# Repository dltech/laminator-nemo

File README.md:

# laminator-nemo
simple replacement board for office laminator with display, temperature and motor control.

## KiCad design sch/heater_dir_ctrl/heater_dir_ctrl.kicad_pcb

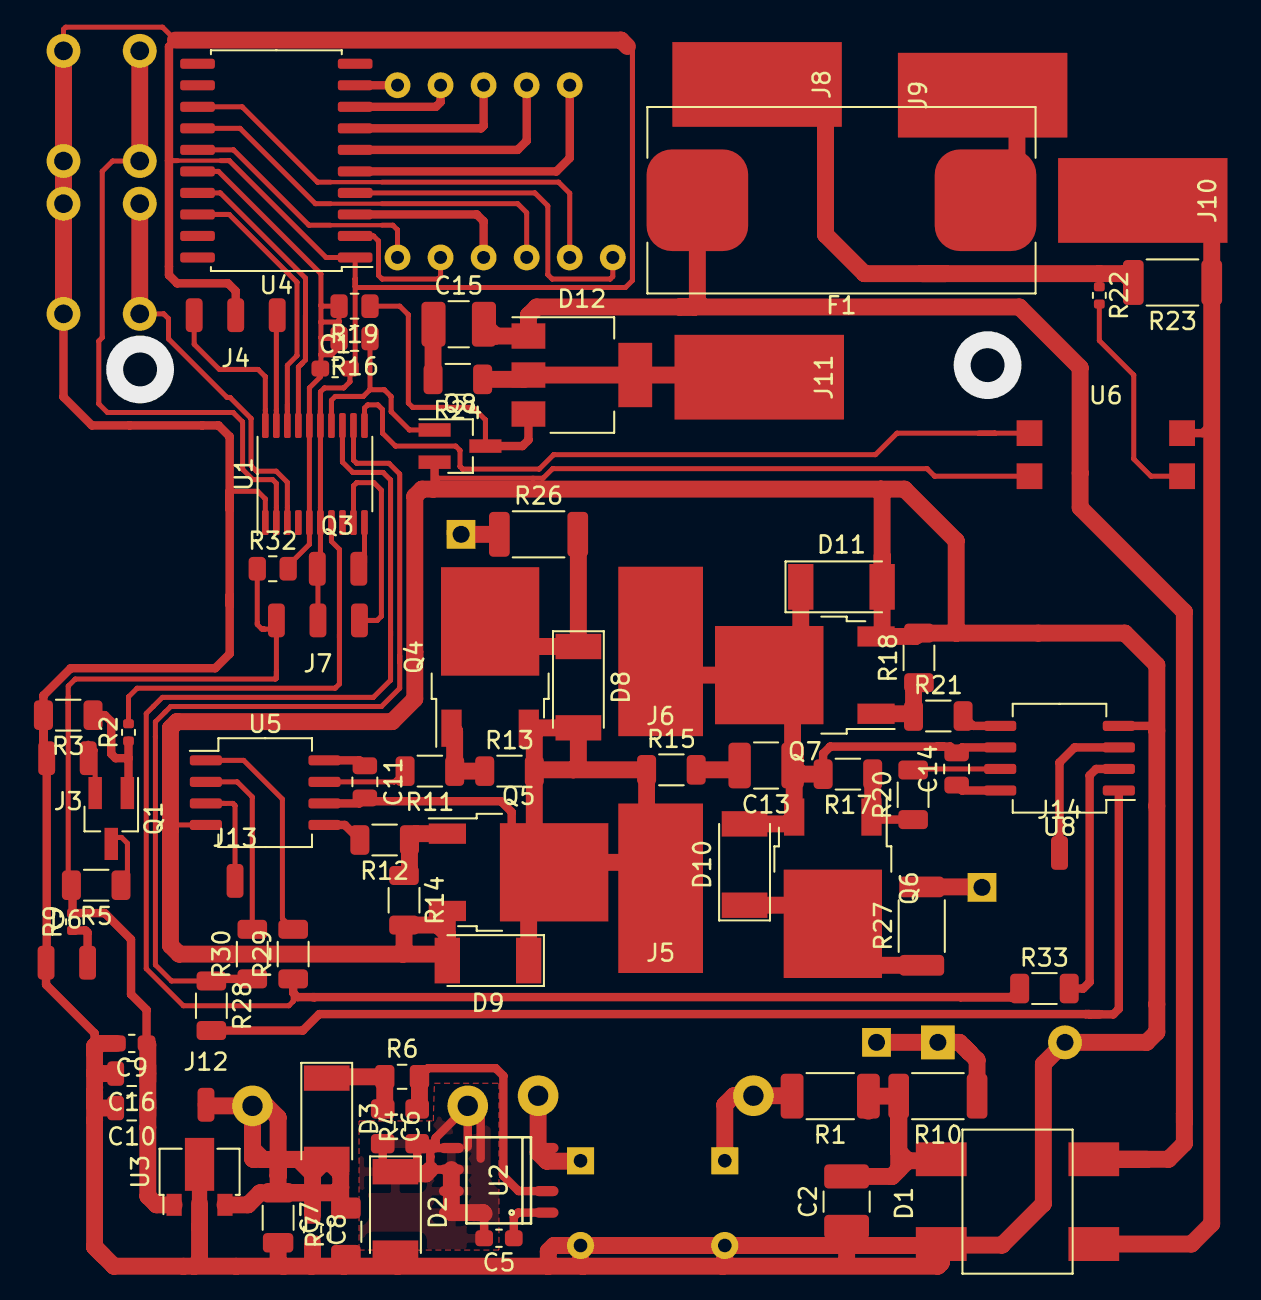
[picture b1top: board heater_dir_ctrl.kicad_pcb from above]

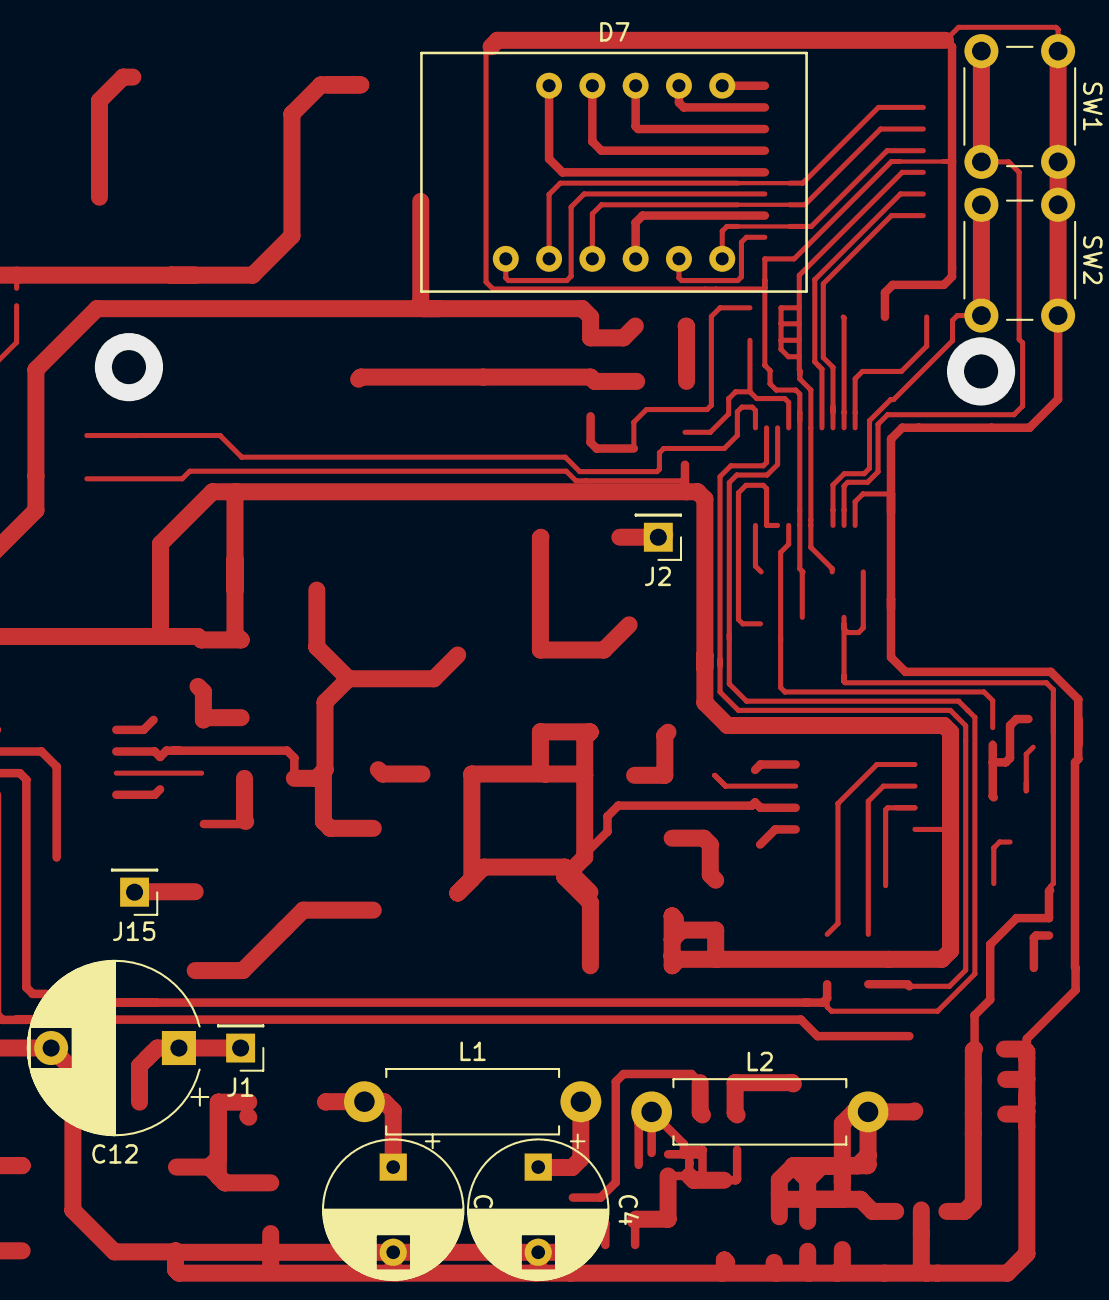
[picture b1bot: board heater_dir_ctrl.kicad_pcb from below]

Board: 2 copper layers, 90 parts (11 on the bottom side), 69 nets.

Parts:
C1, C5, C8, C9: 100n; C_0603_1608Metric_Pad1.05x0.95mm_HandSolder
C2: 0.1; C_1210_3225Metric_Pad1.42x2.65mm_HandSolder
C3, C4: 4.7uF 400V; CP_Radial_D8.0mm_P5.00mm
C6: 1uF; C_0805_2012Metric_Pad1.15x1.40mm_HandSolder
C7: 100uF; C_1206_3216Metric
C10, C11, C14, C16: 10uF; C_0805_2012Metric
C12: 22uF 400V; CP_Radial_D10.0mm_P7.50mm
C13: 100n; C_1210_3225Metric_Pad1.33x2.70mm_HandSolder
C15: 100n; C_1210_3225Metric_Pad1.42x2.65mm_HandSolder
D1: D_Bridge_+-AA; DB-1S
D2: S1M; D_MELF
D3, D8, D9, D10, D11: 1N4007; D_MELF
D6: IR204A; 2WIRE_PADS
D7: LED_3digit; FYT-3631_nonc
D12: Z0109MN; SOT-223
F1: Fuse; Fuseholder_Cylinder-5x20mm_Schurter_OGN-SMD_Horizontal_Open
J1, J2, J15: 300V; PinHeader_1x01_P2.54mm_Vertical
J3: UV; 2WIRE_PADS
J4: SWD; 3WIRE_PADS
J5, J6: motor; SolderWirePad_1x01_SMD_5x10mm
J7: .; 3WIRE_PADS
J8, J9: ac_in; SolderWirePad_1x01_SMD_5x10mm
J10, J11: heater; SolderWirePad_1x01_SMD_5x10mm
J12, J13, J14: 10V; SolderWirePad_1x01_SMD_1x2mm
L1, L2: L; R_Axial_DIN0411_L9.9mm_D3.6mm_P12.70mm_Horizontal
Q1: AO3400; SOT-23_Handsoldering
Q3: Q_Photo_NPN_CE; 2WIRE_PADS
Q4, Q5, Q6, Q7: 2N60; TO-252-2
Q8: DTD114E; SOT-23_Handsoldering
R1: 10; R_2010_5025Metric
R2: 50; R_0402_1005Metric
R3: 50; R_1206_3216Metric
R4: 2.2k; R_0805_2012Metric_Pad1.15x1.40mm_HandSolder
R5, R11, R12, R13, R14, R15, R17, R18, R20, R21, R28, R29, R30, R33: 220; R_1206_3216Metric
R6: 4.7k; R_0805_2012Metric_Pad1.15x1.40mm_HandSolder
R7: 2.2k; R_1206_3216Metric
R9: 1k; R_0402_1005Metric
R10: 100; R_2010_5025Metric
R16, R19: 100k; R_0805_2012Metric
R22: 1к; R_0402_1005Metric
R23, R26, R27: 1; R_2010_5025Metric
R24: 1k; R_1206_3216Metric
R32: 2; R_0805_2012Metric
SW1, SW2: SW_Push; SW_PUSH_6mm
U1: STM32F031F4P6; TSSOP-20_4.4x6.5mm_P0.65mm
U2: LNK306D; SO-8C
U3: L78L33_SOT89; SOT-89-3
U4: TM1637; SOIC-20W_7.5x12.8mm_P1.27mm
U5, U8: L6388; SO-8_5.3x6.2mm_P1.27mm
U6: LTV-817; LTV817

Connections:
+3.3VA: C9.1, C10.1, C16.1, J7.3, R5.2, R9.2, R32.1, U3.1
+3V3: C1.1, R16.2, R19.2, R32.2, U1.5, U1.16, U4.16
+10V: C7.1, C8.1, D3.2, J12.1, J13.1, J14.1, L2.2, R7.2, U3.3, U5.3, U8.3
/LEFT: R28.1, R30.1, U1.12
/RIGHT: R29.1, R33.1, U1.13
DS18B20: J7.1, U1.8, U1.9
GND: C1.2, C2.1, C3.2, C4.2, C7.2, C8.2, C9.2, C10.2, C12.2, C16.2, D1.2, D2.2, D6.1, D9.2, D11.2, J3.2, J4.2, J7.2, Q3.1, Q5.3, Q7.3, Q8.2, R3.2, R7.1, R14.2, R18.2, SW1.1, SW2.1, U1.1, U1.6, U1.15, U3.2, U4.1, U5.4, U6.3, U8.4
LINE: D1.3, J10.1, R23.1, U6.2
NEUT: C15.2, D1.4, D12.1, F1.2
unnamed: C3.1, L1.1, R1.2
unnamed: C4.1, L1.2, U2.4
unnamed: C5.1, U2.1
unnamed: C5.2, C6.2, D2.1, L2.1, R4.1, U2.5, U2.6, U2.7, U2.8
unnamed: C6.1, D3.1, R6.1
unnamed: C11.1, U5.8
unnamed: C11.2, D8.2, D9.1, J5.1, Q4.3, Q5.2, R13.2, R15.1, U5.6
unnamed: C12.1, J1.1, R10.1
unnamed: C13.1, C14.2, D10.2, D11.1, J6.1, Q6.3, Q7.2, R17.2, U8.6
unnamed: C13.2, R15.2
unnamed: C14.1, U8.8
unnamed: C15.1, R24.2
unnamed: D6.2, R9.1
unnamed: D7.1, U4.9
unnamed: D7.2, U4.8
unnamed: D7.3, U4.7
unnamed: D7.4, U4.6
unnamed: D7.5, U4.5
unnamed: D7.7, U4.4
unnamed: D7.8, U4.13
unnamed: D7.9, U4.14
unnamed: D7.10, U4.3
unnamed: D7.11, U4.2
unnamed: D7.12, U4.15
unnamed: D8.1, Q4.2, R26.2
unnamed: D10.1, Q6.2, R27.1
unnamed: D12.2, D12.4, J11.1, R24.1
unnamed: D12.3, Q8.3, R19.1
unnamed: F1.1, J9.1
unnamed: J2.1, R26.1
unnamed: J3.1, Q1.2
unnamed: J4.1, U1.19
unnamed: J4.3, U1.20
unnamed: J8.1, R22.1, R23.2
unnamed: J15.1, R27.2
unnamed: Q1.1, R2.1, R3.1
unnamed: Q1.3, R5.1
unnamed: Q3.2, U1.10
unnamed: Q4.1, R11.1, R13.1
unnamed: Q5.1, R12.1, R14.1
unnamed: Q6.1, R17.1, R20.1
unnamed: Q7.1, R18.1, R21.1
unnamed: Q8.1, R16.1, U1.14
unnamed: R2.2, U1.7
unnamed: R4.2, R6.2, U2.2
unnamed: R11.2, U5.7
unnamed: R12.2, U5.5
unnamed: R20.2, U8.7
unnamed: R21.2, U8.5
unnamed: R22.2, U6.1
unnamed: R28.2, U8.1
unnamed: R29.2, U5.1
unnamed: R30.2, U5.2
unnamed: R33.2, U8.2
unnamed: SW1.2, U1.2
unnamed: SW2.2, U1.3
unnamed: U1.11, U6.4
unnamed: U1.17, U4.17
unnamed: U1.18, U4.18
VPP: C2.2, D1.1, R1.1, R10.2

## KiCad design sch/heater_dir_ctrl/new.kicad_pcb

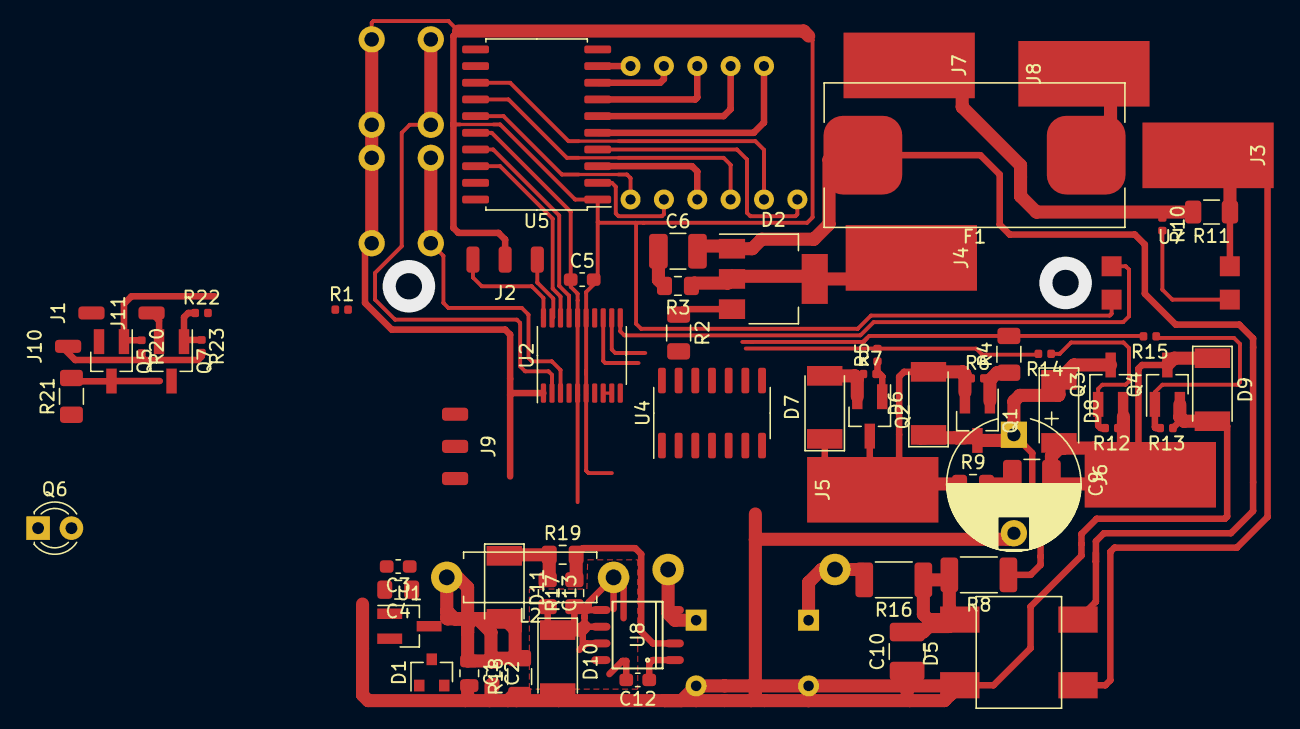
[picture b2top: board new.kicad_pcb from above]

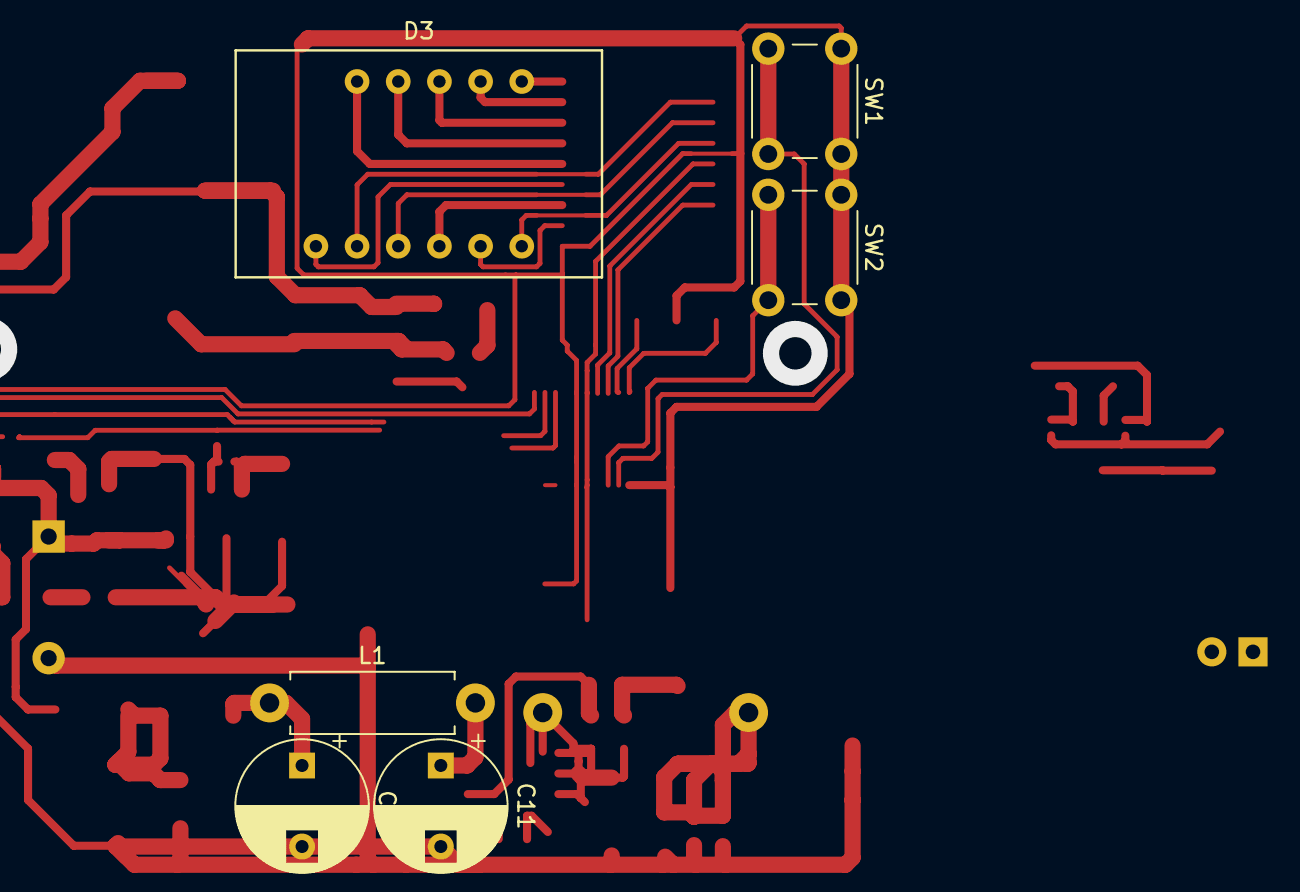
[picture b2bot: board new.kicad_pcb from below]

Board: 2 copper layers, 75 parts (6 on the bottom side), 60 nets.

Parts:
C1: 10uF; C_0805_2012Metric
C2, C3, C5, C12: 100n; C_0603_1608Metric_Pad1.05x0.95mm_HandSolder
C4: 10uF; C_0805_2012Metric_Pad1.15x1.40mm_HandSolder
C6, C8: 100n; C_1210_3225Metric_Pad1.42x2.65mm_HandSolder
C7, C11: 4.7uF 400V; CP_Radial_D8.0mm_P5.00mm
C9: 22uF 400V; CP_Radial_D10.0mm_P7.50mm
C10: 0.1; C_1210_3225Metric_Pad1.42x2.65mm_HandSolder
C13: 1uF; C_0805_2012Metric_Pad1.15x1.40mm_HandSolder
D1: D_Zener; D_SOT-23_ANK
D2: Z0109MN; SOT-223
D3: LED_3digit; FYT-3631_nonc
D5: D_Bridge_+-AA; DB-1S
D6, D7, D8, D9, D11: 1N4007; D_MELF
D10: S1M; D_MELF
F1: Fuse; Fuseholder_Cylinder-5x20mm_Schurter_OGN-SMD_Horizontal_Open
J1: UV light; SolderWirePad_1x01_SMD_1x2mm
J2: SWD; 3WIRE_PADS
J3, J4: heater; SolderWirePad_1x01_SMD_5x10mm
J5, J6: motor; SolderWirePad_1x01_SMD_5x10mm
J7, J8: ac_in; SolderWirePad_1x01_SMD_5x10mm
J9: .; 3WIRE_PADS
J10: main; SolderWirePad_1x01_SMD_1x2mm
J11: flashlight; SolderWirePad_1x01_SMD_1x2mm
L1, L2: L; R_Axial_DIN0411_L9.9mm_D3.6mm_P12.70mm_Horizontal
Q1, Q2, Q3, Q4: MMBTA42; SOT-23_Handsoldering
Q5, Q7: AO3400; SOT-23_Handsoldering
Q6: Q_Photo_NPN_CE; LED_D3.0mm
R1, R20, R22, R23: 50; R_0402_1005Metric
R2, R4: 220; R_1206_3216Metric
R3: 1k; R_0805_2012Metric_Pad1.15x1.40mm_HandSolder
R5, R6, R7, R12, R13, R14, R15: 220; R_0402_1005Metric
R8: 100; R_2010_5025Metric
R9: 220; R_0805_2012Metric_Pad1.15x1.40mm_HandSolder
R10: 1к; R_0402_1005Metric
R11: 1; R_1206_3216Metric
R16: 10; R_2010_5025Metric
R17: 2.2k; R_0805_2012Metric_Pad1.15x1.40mm_HandSolder
R18: 2.2k; R_1206_3216Metric
R19: 4.7k; R_0805_2012Metric_Pad1.15x1.40mm_HandSolder
R21: 390; R_1206_3216Metric
SW1, SW2: SW_Push; SW_PUSH_6mm
U1: XC6206-33; SOT-23_Handsoldering
U2: STM32F031F4Px; TSSOP-20_4.4x6.5mm_P0.65mm
U4: 4069; SOIC-14_3.9x8.7mm_P1.27mm
U5: TM1637; SOIC-20W_7.5x12.8mm_P1.27mm
U7: LTV-817; LTV817
U8: LNK306D; SO-8C

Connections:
+3V3: C3.1, C4.1, C5.1, J9.3, U1.2, U2.5, U2.16, U4.14, U5.16
+5V: C1.1, C2.1, D1.1, D11.2, L2.2, R18.2, R21.1, U1.3
DS18B20: J9.1, U2.8, U2.9
GND: C5.2, C9.2, C10.1, D7.2, D9.2, J2.2, J9.2, J10.1, Q2.2, Q4.2, Q6.2, R7.1, R13.1, R20.2, R23.2, SW1.1, SW2.1, U2.1, U2.15, U4.3, U4.5, U4.7, U5.1, U7.3
LINE: D5.3, J3.1, R11.1, U7.2
NEUT: C6.2, D2.1, D5.4, F1.2
unnamed: C1.2, C2.2, C3.2, C4.2, C7.2, C11.2, D1.2, D5.2, D10.2, R18.1, U1.1
unnamed: C6.1, R3.2
unnamed: C7.1, L1.1, R16.2
unnamed: C8.1, D8.2, D9.1, J6.1, Q3.2, Q4.3, R12.1
unnamed: C8.2, R9.2
unnamed: C9.1, D6.1, D8.1, Q1.3, Q3.3, R8.1
unnamed: C11.1, L1.2, U8.4
unnamed: C12.1, U8.1
unnamed: C12.2, C13.2, D10.1, L2.1, R17.1, U8.5, U8.6, U8.7, U8.8
unnamed: C13.1, D11.1, R19.1
unnamed: D2.2, D2.4, J4.1, R3.1
unnamed: D2.3, R2.1
unnamed: D3.1, U5.9
unnamed: D3.2, U5.8
unnamed: D3.3, U5.7
unnamed: D3.4, U5.6
unnamed: D3.5, U5.5
unnamed: D3.7, U5.4
unnamed: D3.8, U5.13
unnamed: D3.9, U5.14
unnamed: D3.10, U5.3
unnamed: D3.11, U5.2
unnamed: D3.12, U5.15
unnamed: D6.2, D7.1, J5.1, Q1.2, Q2.3, R6.1, R9.1
unnamed: F1.1, J8.1
unnamed: J1.1, Q5.2
unnamed: J2.1, U2.19
unnamed: J2.3, U2.20
unnamed: J7.1, R10.1, R11.2
unnamed: J11.1, Q7.2
unnamed: Q1.1, R4.1, R6.2
unnamed: Q2.1, R5.1, R7.2
unnamed: Q3.1, R12.2, R14.1
unnamed: Q4.1, R13.2, R15.1
unnamed: Q5.1, R1.1, R20.1
unnamed: Q5.3, Q7.3, R21.2
unnamed: Q6.1, U2.7
unnamed: Q7.1, R22.1, R23.1
unnamed: R1.2, U2.14, U4.1
unnamed: R2.2, U4.8
unnamed: R10.2, U7.1
unnamed: R5.2, R14.2, U4.12
unnamed: R4.2, R15.2, U4.10
unnamed: R17.2, R19.2, U8.2
unnamed: R22.2, U4.2
unnamed: SW1.2, U2.2
unnamed: SW2.2, U2.3
unnamed: U2.10, U4.13
unnamed: U2.11, U7.4
unnamed: U2.12, U4.9
unnamed: U2.13, U4.11
unnamed: U2.17, U5.17
unnamed: U2.18, U5.18
VPP: C10.2, D5.1, R8.2, R16.1

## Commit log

2020-12-02 digits are working, sinus output too
2021-04-07 add ds18b20 hardware
2021-04-07 ds 40%
2021-04-09 ds 60%
2021-04-11 ds compiled (not tested)
2021-04-12 ds init seq ok
2021-04-12 ds18b20 tested, working
2021-04-13 sch w new transistors
2021-04-16 PCB with new transistors
2021-04-17 didn't fit
2021-05-07 drivers
2021-05-07 upd scenario
2021-05-07 commas
2021-05-10 board ok
2021-05-22 some corrections
2021-05-23 program ds18b20, usart based fails after 60C
2021-05-27 78l instead of 1117, synchronized pwm ok, not tested
2021-05-28 narkoman
2022-04-14 new drivers
